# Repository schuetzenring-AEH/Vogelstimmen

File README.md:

# Vogelstimmenkasten – Waldlehrpfad (Rev 2)

Neubau der Elektronik eines Vogelstimmenkastens für den Waldlehrpfad der Kolpingfamilie.

## Überblick

Besucher können per Knopfdruck (8 beleuchtete Taster) verschiedene Vogelstimmen anhören. Die Elektronik ist auf **null Ruhestrom** optimiert (Hardware-Latch) und wird über eine 12-V-Autobatterie betrieben.

**Architektur:** DY-SV17F (IO-Trigger, integrierter Class-D-Verstärker) + Hardware-Latch (MOSFET-Selbsthaltung)

## Projektstatus

| Phase | Status |
|-------|--------|
| Anforderungen | ✅ fertig |
| Systemarchitektur (BDD/IBD) | ✅ fertig |
| Schaltplan-Dokumentation Rev 2 | ✅ fertig |
| BOM-Verfügbarkeit (LCSC/JLCPCB) | ✅ geprüft |
| Digitaler Zwilling (Bauteilebene) | ✅ `docs/digitaler_zwilling.md` |
| KiCad-Schaltplan (+ VGS-Zener D11/D12) | ✅ verdrahtet |
| PCB Rev 2.4 + Respin F-01…F-05 | ✅ Working-PCB DRC/ERC 0 Fehler |
| Gerber / BOM / CPL | ✅ `hardware/V2.5-final/` (FREIGABE MIT AUFLAGEN) |
| M04-Review / Adversarial | ✅ F-01…F-09 dispositioniert; Proto-Auflagen |
| Fertigung & Inbetriebnahme | ▶️ JLCPCB bestellbar; Proto messen vor Serie |
| MBSE-Showcase (USB) | ✅ `showcase/` + `dist/Vogelstimmen-MBSE-USB.zip` |

**Reviewer-Einstieg:** [docs/reviewer_handoff.md](docs/reviewer_handoff.md) · Checkliste [docs/review_checkliste_m04.md](docs/review_checkliste_m04.md)  
Details: **[docs/zwischenstand.md](docs/zwischenstand.md)**

## Projektstruktur

| Ordner | Inhalt |
|--------|--------|
| `docs/` | Lastenheft, Architektur, ADRs, Traceability, Zwilling, Zwischenstand |
| `hardware/V2.5-final/` | Fertigungspaket Rev 2.5 (Gerber, BOM, CPL, KiCad, PDFs) |
| `simulation/` | Interaktive Platinen-Simulation (HTML5) |
| `showcase/` | **MBSE-Präsentation** (offline Website) — `START_SHOWCASE.bat` |
| `mbse/` | Impact-Analyse, Audit, SysML/JSON-Export — URL `/mbse/` |
| `dist/` | USB-ZIP nach `tools/package_mbse_usb.ps1` |
| `rev1_archiv/` | Rev-1-Archiv (Lessons Learned) |

## Technische Eckdaten

- **Audio-Modul:** DY-SV17F (8× IO-Trigger, Mode 0, 5W Class-D, USB-Upload)
- **Versorgung:** 12V Bleiakku → TPS62163 Buck → 5V
- **Stromsparen:** Hardware-Latch — Idle ≈12 µA (R6=470 kΩ, E-RPP-01)
- **Schutz:** Verpolung SI2301+**D11 Zener 6,2 V**, Latch Q1+**D12**, TVS SMAJ15A, PTC 1A/24V
- **Zähler:** Kübler K07.90 (5V DC, elektromechanisch, Anzeige oben, zählt Aufweck-Events)
- **Taster-LEDs:** 8× beleuchtete Taster (6–24V LEDs über 12V_SW Rail)
- **Audioformat:** MP3/WAV direkt per USB auf DY-SV17F laden
- **Digitaler Zwilling:** [docs/digitaler_zwilling.md](docs/digitaler_zwilling.md)

## Rev 1 → Rev 2: Lessons Learned

Rev 1 hatte Probleme mit Spannungsfestigkeit (U4/U5 Burnout bei 12V), Bauteil-Verfügbarkeit und fehlendem Verifikationsansatz. Rev 2 verwendet:
- MBSE / V-Modell mit Traceability
- Durchgängige Spannungsprüfung aller Bauteile
- BOM-Verfügbarkeit vorab bei LCSC geprüft
- Digitaler Zwilling zur Logikverifikation

## Voraussetzungen (Entwicklung)

- [KiCad 10](https://www.kicad.org/) – Schaltplan/PCB
- Python 3 – lokale Simulation (`python simulation/serve.py`) oder `START_SHOWCASE.bat` / `START_MBSE.bat`
- [LTspice](https://www.analog.com/en/resources/design-tools-and-calculators/ltspice-simulator.html) – analoge Teilschaltungen (optional)

## Lizenz

Dieses Projekt ist für den internen Gebrauch der Kolpingfamilie bestimmt.

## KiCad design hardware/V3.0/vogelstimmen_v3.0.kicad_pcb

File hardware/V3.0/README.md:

# Fertigungspaket Rev 3.0

**Datum:** 11. August 2026  
**Projekt:** Soundplatine Waldlehrpfad · Kolping Alteglofsheim  
**KiCad:** 10.0.4 · `vogelstimmen_v3.0.kicad_*`

## Freigabe-Stand

| Check | Ergebnis |
|-------|----------|
| **DRC** | **0 Fehler**, 0 unverbunden — 1 Warnung U2 Footprint-Lib (`DRC_v3.0_final.rpt`) |
| **ERC** | siehe `ERC_v3.0_final.rpt` |
| **Widerstände** | alle **15×** `R_0603_1608Metric`, Pad-Pitch **1,65 mm** (kein 0402) |
| **Zähler** | Hengstler 0.635.128 + One-Shot (C20/R20/R21/D23/Q7/D10) |

## JLCPCB — Upload (nur SMD)

| Datei | Zweck |
|-------|--------|
| **`vogelstimmen_v3.0-Gerber.zip`** | Gerber + Drill (auch Ordner `Gerber/`) |
| **`JLCPCB_BOM.csv`** | SMT-BOM inkl. One-Shot + 0603 Basic LCSC |
| **`JLCPCB_CPL.csv`** | Pick-and-Place (52 SMT-Teile) — **diese** hochladen |
| `JLCPCB_CPL_minimal.csv` | Fallback (5 Spalten), falls volles Format scheitert |

**Nicht** an JLCPCB hochladen: `HAND_BESTUECKUNG.csv`, KiCad-Roh-CPL mit Handteilen.

**Platinen-Parameter (empfohlen):** 2 Layer · 1,6 mm · HASL oder ENIG · Clearance 0,2 mm · **Min. Bahnbreite 0,3 mm** · Via 0,6/0,3 mm.

## Handbestückung (nicht in JLCPCB-BOM)

Datei: **`HAND_BESTUECKUNG.csv`** · RS-Warenkorb: **`docs/rs_bestellliste.md`**

| Ref | Teil | Assembly | RS |
|-----|------|----------|-----|
| **U2** | DY-SV17F | HAND | nicht bei RS |
| **J5** | Hengstler **0.635.128** (nicht 0.635.132) | HAND | **312-022** |
| **J1, J2, J6** | Phoenix MPT 0,5/2 **1725656** | HAND | **220-4260** |
| **J3, J4** | Phoenix MPT 0,5/8 **1725711** | HAND | **220-4327** |
| **TP1–TP5** | Testpads | DNP | — |

## Widerstände — Package-Check (E-R0603)

| Refs | Wert | Footprint PCB | LCSC | Package |
|------|------|---------------|------|---------|
| R1,R2,R13,R20 | 100k | R_0603_1608Metric | C25803 | 0603 Basic |
| R3,R4,R9 | 10k | R_0603_1608Metric | C25804 | 0603 Basic |
| R5 | 0R | R_0603_1608Metric | C21189 | 0603 Basic |
| R6 | 470k | R_0603_1608Metric | C23178 | 0603 Basic |
| R7,R8,R11 | 4.7k | R_0603_1608Metric | C23162 | 0603 Basic |
| R10 | 1k | R_0603_1608Metric | C21190 | 0603 Basic |
| R12 | 10R | R_0603_1608Metric | C22859 | 0603 Basic |
| R21 | 100R | R_0603_1608Metric | C25796 | 0603 Basic |

Pads gemessen: **0,80×0,95 mm**, Mittenabstand **1,65 mm** → passt zu 0603 (0402 wäre ~1,0 mm).

## Änderungen gegenüber 2.5

| Thema | 2.5 | 3.0 |
|-------|-----|-----|
| Widerstände | Pads oft 0402 / LCSC 0603 → Reject | **0603 Pads + 0603 Basic LCSC** |
| Zähler J5 | Kübler K07.90 | **Hengstler 0.635.128** + One-Shot ~80 ms |
| Form | Panel / groß | Body **25,2×31 mm**, 4 Pins 15,24×25,4 mm |

## Paketinhalt

| Datei / Ordner | Inhalt |
|----------------|--------|
| `Gerber/` | Einzel-Gerber + PTH/NPTH Drill |
| `vogelstimmen_v3.0-Gerber.zip` | **Upload-Paket** |
| `JLCPCB_BOM.csv` / `JLCPCB_CPL.csv` | SMT Assembly |
| `HAND_BESTUECKUNG.csv` | Handteile |
| `RS_SCHNELLBESTELLUNG.csv` | RS-Warenkorb 1 Platine |
| `docs/rs_bestellliste.md` | RS-Links, Warnungen, 10× |
| `vogelstimmen_v3.0-schematic.pdf` | Schaltplan |
| `vogelstimmen_v3.0-pcb.pdf` | Layout |
| `docs/` | ADRs, Schaltplan, BOM-Checkliste |
| `tools/export_fab.py` | Re-Export Gerber/CPL/PDF |

## Re-Export

```powershell
& "C:\Program Files\KiCad\10.0\bin\python.exe" hardware\V3.0\tools\export_fab.py
```

## Parallel bestellen

1. JLCPCB: Gerber.zip + BOM + CPL (SMD Assembly)
2. **RS** Schnellbestellung: `RS_SCHNELLBESTELLUNG.csv` (Hengstler 312-022 + MPT) — Zähler oft Wochen
3. DY-SV17F (AliExpress; nicht bei RS)

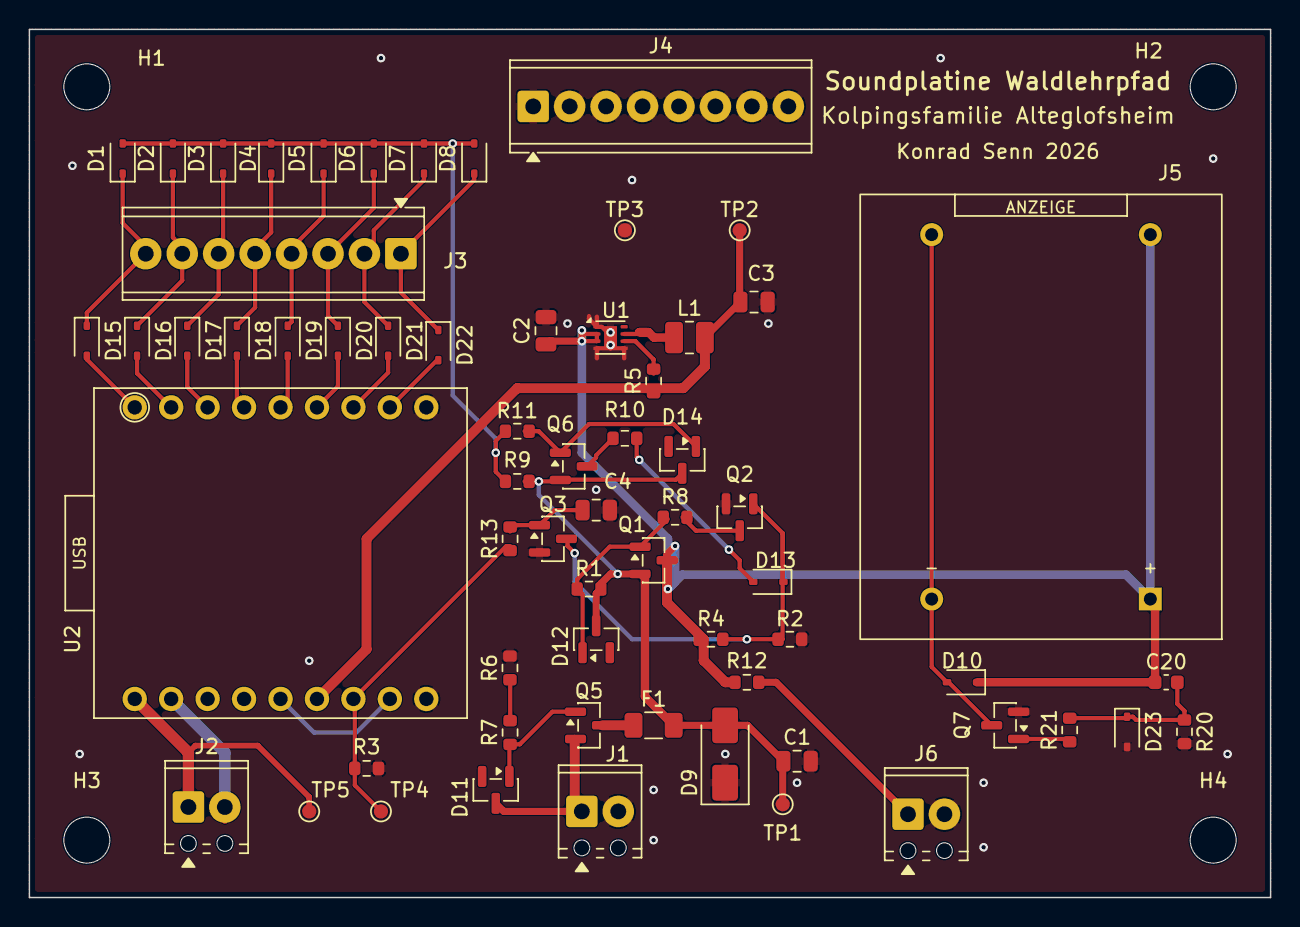
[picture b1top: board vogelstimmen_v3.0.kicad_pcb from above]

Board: 2 copper layers, 86.5 x 60.5 mm, 68 parts (0 on the bottom side), 42 nets.

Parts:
C1, C2: 10u/25V; C_0805_2012Metric
C3: 22u/10V; C_0805_2012Metric
C4: 4.7u/16V; C_0805_2012Metric
C20: 1u/25V; C_0603_1608Metric
D1, D2, D3, D4, D5, D6, D7, D8, D10, D13, D15, D16, D17, D18, D19, D20, D21, D22, D23: 1N4148WS; D_SOD-323
D9: SMAJ15A; D_SMA
D11, D12, D14: BZX84C6V2
F1: 1A/24V; Fuse_1206_3216Metric
H1, H2, H3, H4: MountingHole_3.2mm_M3
J1: MPT-0,5/2 BAT; TerminalBlock_Phoenix_MPT-0,5-2-2.54_1x02_P2.54mm_Horizontal
J2: MPT-0,5/2 SPK; TerminalBlock_Phoenix_MPT-0,5-2-2.54_1x02_P2.54mm_Horizontal
J3: MPT-0,5/8 IO; TerminalBlock_Phoenix_MPT-0,5-8-2.54_1x08_P2.54mm_Horizontal
J4: MPT-0,5/8 GND; TerminalBlock_Phoenix_MPT-0,5-8-2.54_1x08_P2.54mm_Horizontal
J5: Hengstler 0.635.128; CNT_HENGSTLER_635
J6: MPT-0,5/2 LED; TerminalBlock_Phoenix_MPT-0,5-2-2.54_1x02_P2.54mm_Horizontal
L1: 2.2uH; L_1008_2520Metric
Q1, Q5, Q6: SI2301; SOT-23
Q2, Q3: 2N7002; SOT-23
Q7: AO3400; SOT-23
R1, R2, R13, R20: 100k; R_0603_1608Metric
R3, R4, R9: 10k; R_0603_1608Metric
R5: 0R; R_0603_1608Metric
R6: 470k; R_0603_1608Metric
R7, R8, R11: 4.7k; R_0603_1608Metric
R10: 1k; R_0603_1608Metric
R12: 10; R_0603_1608Metric
R21: 100R; R_0603_1608Metric
TP1: 12V_PROT; TestPoint_Pad_D1.0mm
TP2: 5V; TestPoint_Pad_D1.0mm
TP3: GND; TestPoint_Pad_D1.0mm
TP4: BUSY; TestPoint_Pad_D1.0mm
TP5: SPK+; TestPoint_Pad_D1.0mm
U1: TPS62163; WSON-8-1EP_2x2mm_P0.5mm_EP0.9x1.6mm
U2: DY-SV17F

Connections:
/5V: C3.1, L1.2, R5.1, TP2.1 (Pin_1_1), U2.13 (V5)
/12V_LED: J6.1, R12.2
/12V_PROT: C1.1, D9.2 (A2), D12.1, D14.1, F1.2, Q1.2 (S), Q6.2, R1.2, R9.1, TP1.1 (Pin_1_1)
/12V_SW: C2.1, C20.1, D10.1 (K), J5.1, Q1.3 (D), R4.1, R12.1, U1.2 (VIN), U1.3 (EN)
/BAT+: D11.1, J1.1, Q5.2 (S)
/BTN_OR: D1.2 (A), D2.2 (A), D3.2 (A), D4.2 (A), D5.2 (A), D6.2 (A), D7.2 (A), D8.2 (A), R9.2, R11.1
/BUSY: R3.1, R13.1, TP4.1 (Pin_1_1), U2.12 (BUSY)
/CNT_GATE: Q7.1, R21.1
/CNT_LO: D10.2 (A), J5.2, Q7.3
/CNT_PULSE: C20.2, D23.1, R20.1, R21.2
/GND: C1.2, C2.2, C3.2, C4.2, D9.1 (A1), D23.2, J1.2, J4.1, J4.2, J4.3, J4.4, J4.5, J4.6, J4.7, J4.8, J6.2, Q2.2 (S), Q3.2 (S), Q7.2, R2.2, R3.2, R6.2, R20.2, TP3.1 (Pin_1_1), U1.1 (PGND), U1.4 (AGND), U1.5 (FB), U1.9 (EP), U2.9 (GND), U2.10 (CON1)
/IO0: D1.1 (K), D15.1 (K), J3.8
/IO0_M: D15.2 (A), U2.1 (IO0)
/IO1: D2.1 (K), D16.1 (K), J3.7
/IO1_M: D16.2 (A), U2.2 (IO1)
/IO2: D3.1 (K), D17.1 (K), J3.6
/IO2_M: D17.2 (A), U2.3 (IO2)
/IO3: D4.1 (K), D18.1 (K), J3.5
/IO3_M: D18.2 (A), U2.4 (IO3)
/IO4: D5.1 (K), D19.1 (K), J3.4
/IO4_M: D19.2 (A), U2.5 (IO4)
/IO5: D6.1 (K), D20.1 (K), J3.3
/IO5_M: D20.2 (A), U2.6 (IO5)
/IO6: D7.1 (K), D21.1 (K), J3.2
/IO6_M: D21.2 (A), U2.7 (IO6)
/IO7: D8.1 (K), D22.1 (K), J3.1
/IO7_M: D22.2 (A), U2.8 (IO7)
/LATCH_GATE: Q2.3 (D), R8.2
/LATCH_SET: D13.1, Q2.1 (G), Q3.3 (D), R2.1, R4.2
/Q1_GATE: D12.2, Q1.1 (G), R1.1, R8.1
/Q3_GATE: C4.1, Q3.1 (G), R13.2
/Q5_GATE: D11.2, Q5.1 (G), R7.1
/Q5_G_PD: R6.1, R7.2
/Q6_GATE: D14.2, Q6.1, R11.2
/RPP_OUT: F1.1, Q5.3 (D)
/SET_DRV: Q6.3, R10.1
/SET_PULSE: D13.2, R10.2
/SPK+: J2.1, TP5.1 (Pin_1_1), U2.18 (SPK+)
/SPK-: J2.2, U2.17 (SPK-)
/SW: L1.1, U1.7 (SW)
/V33: U2.11 (CON2), U2.14 (V33)
/VOS: R5.2, U1.6 (VOS)

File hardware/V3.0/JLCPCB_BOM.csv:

Comment,Designator,Footprint,LCSC Part #
10uF/25V 0805,"C1,C2",C_0805_2012Metric,C440198
22uF/10V 0805,C3,C_0805_2012Metric,C45783
4.7uF/16V 0805,C4,C_0805_2012Metric,C1779
1uF/25V 0603 Basic,C20,C_0603_1608Metric,C23630
1N4148WS,"D1,D2,D3,D4,D5,D6,D7,D8,D10,D13,D15,D16,D17,D18,D19,D20,D21,D22,D23",D_SOD-323,C118873
SMAJ15A,D9,D_SMA,C113958
BZX84C6V2,"D11,D12,D14",SOT-23,C179522
PTC 1A/24V 1206,F1,Fuse_1206_3216Metric,C2760272
2.2uH 1008,L1,L_1008_2520Metric,C88527
SI2301CDS,"Q1,Q5,Q6",SOT-23,C10487
2N7002LT1G,"Q2,Q3",SOT-23,C16338
AO3400,Q7,SOT-23,C20917
100k 0603 Basic,"R1,R2,R13,R20",R_0603_1608Metric,C25803
0R 0603 Basic,R5,R_0603_1608Metric,C21189
10k 0603 Basic,"R3,R4,R9",R_0603_1608Metric,C25804
10R 0603 Basic,R12,R_0603_1608Metric,C22859
100R 0603 Basic,R21,R_0603_1608Metric,C25796
470k 0603 Basic,R6,R_0603_1608Metric,C23178
4.7k 0603 Basic,"R7,R8,R11",R_0603_1608Metric,C23162
1k 0603 Basic,R10,R_0603_1608Metric,C21190
TPS62163DSGR,U1,WSON-8-1EP_2x2mm,C97534

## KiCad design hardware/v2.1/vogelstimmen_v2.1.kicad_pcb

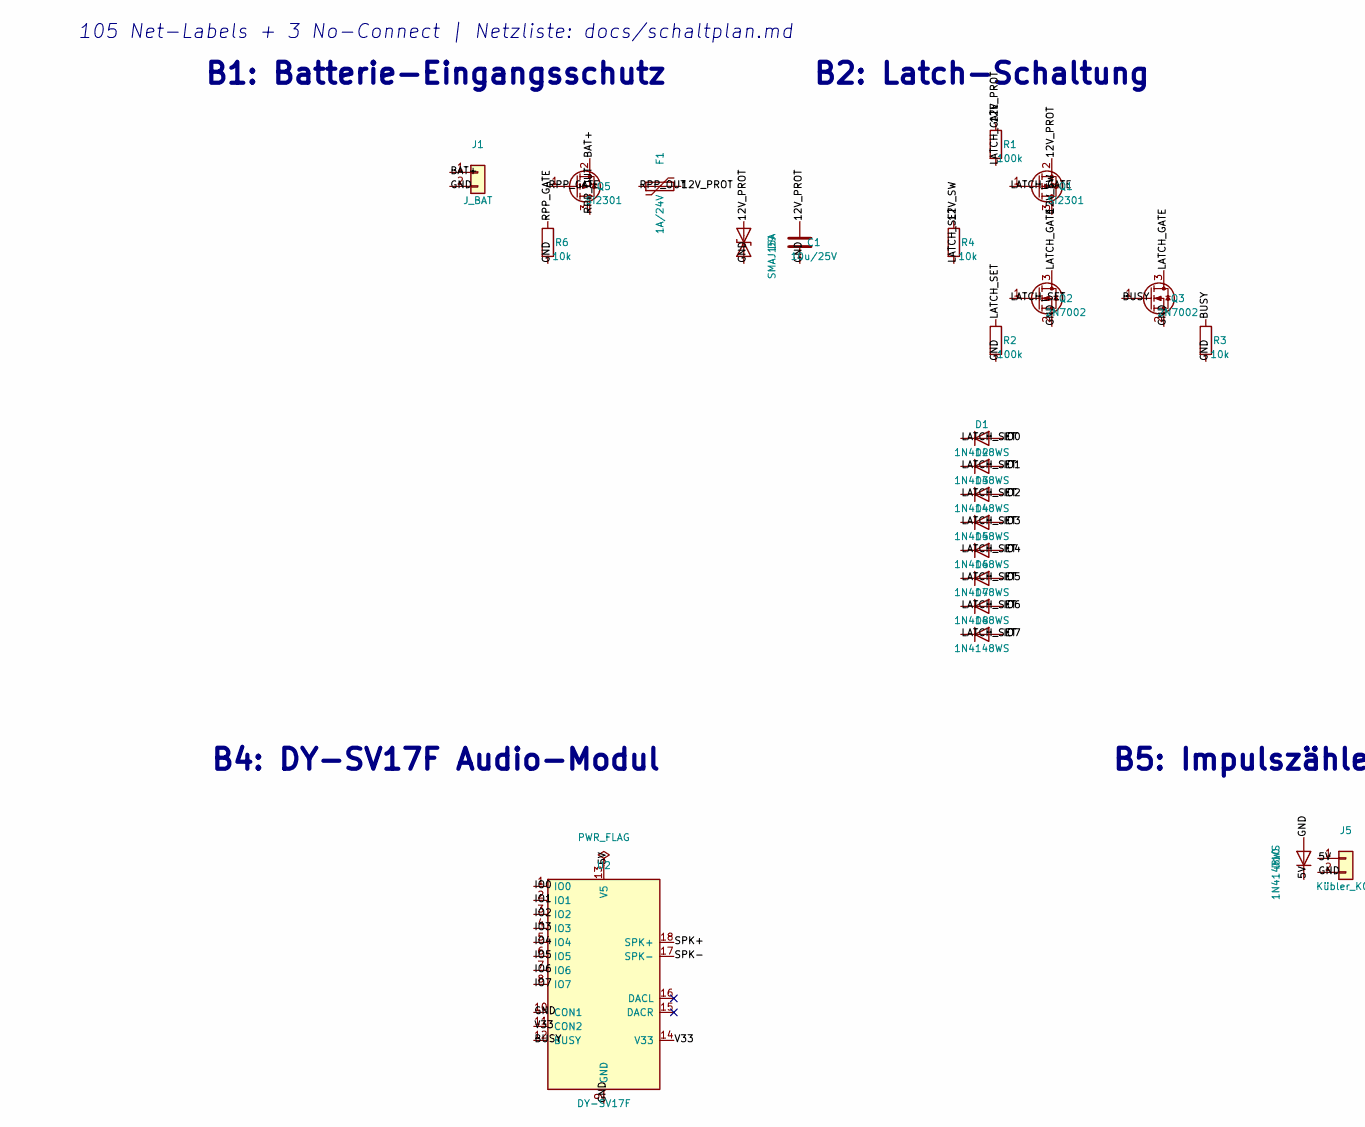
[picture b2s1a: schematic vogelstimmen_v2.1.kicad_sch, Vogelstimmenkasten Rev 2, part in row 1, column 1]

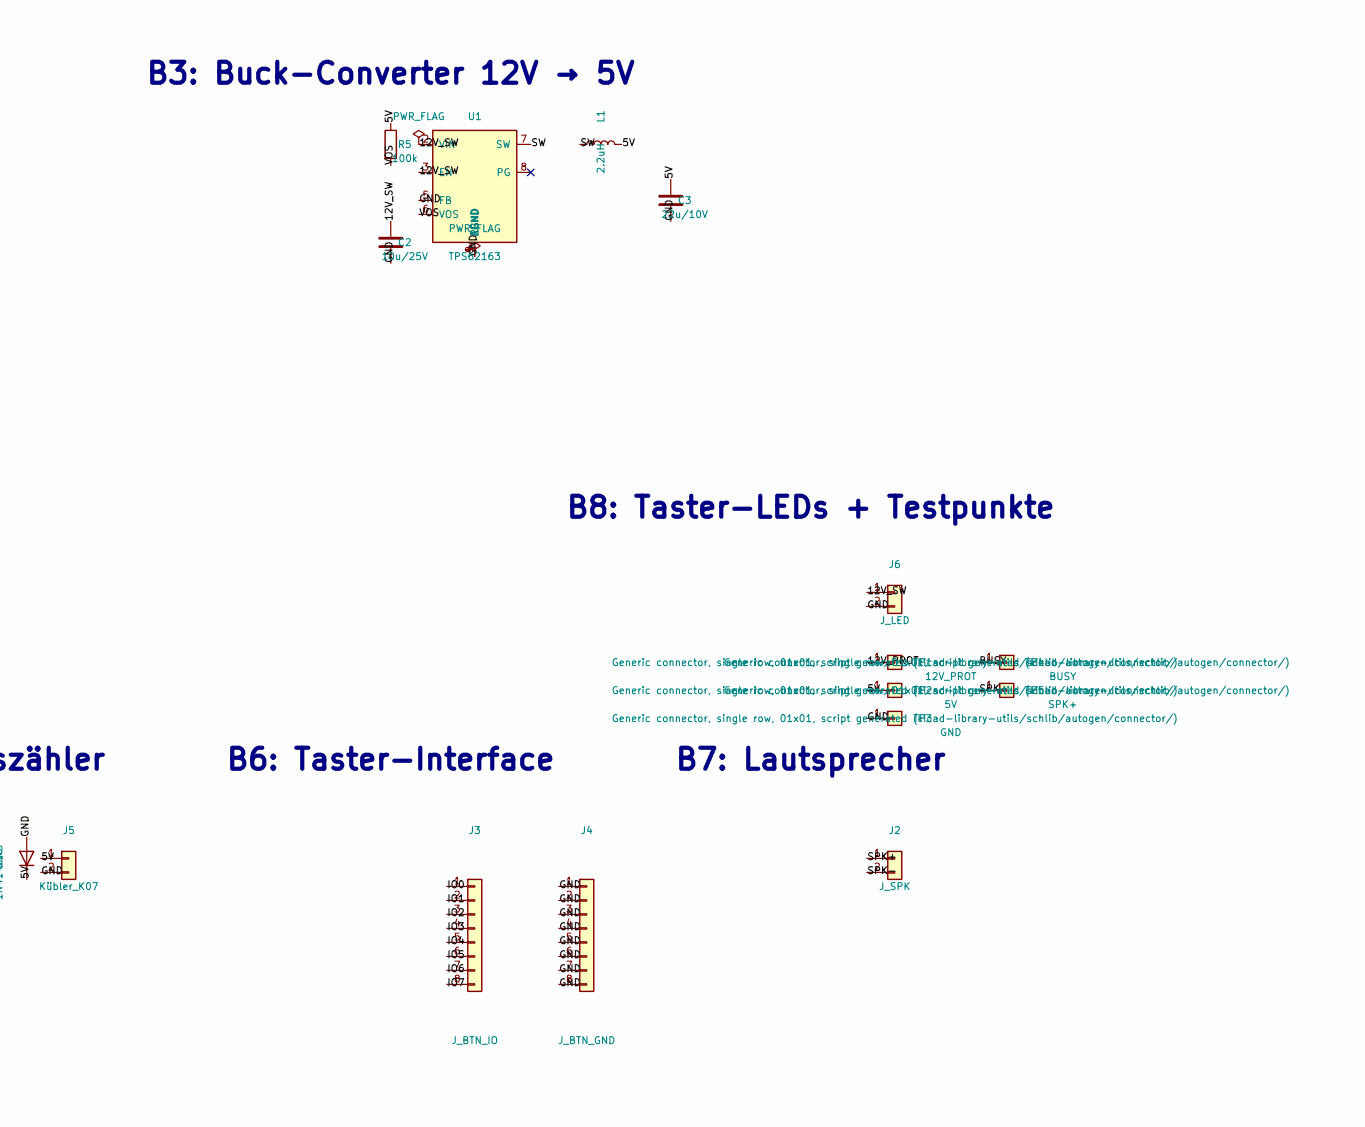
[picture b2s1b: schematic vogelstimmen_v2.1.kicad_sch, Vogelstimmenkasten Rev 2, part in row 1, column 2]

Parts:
C1, C2: 10u/25V; C_0805_2012Metric
C3: 22u/10V; C_0805_2012Metric
D1, D2, D3, D4, D5, D6, D7, D8, D10: 1N4148WS; D_SOD-323; LCSC C118873
D9: SMAJ15A; D_SMA; LCSC C113958
F1: 1A/24V; Fuse_1206_3216Metric; LCSC C2760272
J1: J_BAT; PinHeader_1x02_P2.54mm_Vertical
J2: J_SPK; PinHeader_1x02_P2.54mm_Vertical
J3: J_BTN_IO; PinHeader_1x08_P2.54mm_Vertical
J4: J_BTN_GND; PinHeader_1x08_P2.54mm_Vertical
J5: Kübler_K07; PinHeader_1x02_P2.54mm_Vertical
J6: J_LED; PinHeader_1x02_P2.54mm_Vertical
L1: 2.2uH; L_1008_2520Metric; LCSC C88527
Q1, Q5: SI2301; SOT-23; LCSC C10487
Q2, Q3: 2N7002; SOT-23; LCSC C16338
R1, R2, R5: 100k; R_0402_1005Metric
R3, R4, R6: 10k; R_0402_1005Metric
TP1: 12V_PROT; TestPoint_Pad_D1.0mm
TP2: 5V; TestPoint_Pad_D1.0mm
TP3: GND; TestPoint_Pad_D1.0mm
TP4: BUSY; TestPoint_Pad_D1.0mm
TP5: SPK+; TestPoint_Pad_D1.0mm
U1: TPS62163; WSON-8-1EP_2x2mm_P0.5mm_EP0.9x1.6mm; LCSC C97534
U2: DY-SV17F

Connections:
/5V: C3.1, D10.1 (K), J5.1, L1.2, R5.1, TP2.1 (Pin_1_1), U2.13 (V5)
/12V_PROT: C1.1, D9.2 (A2), F1.2, Q1.2 (S), R1.1, TP1.1 (Pin_1_1)
/12V_SW: C2.1, J6.1, Q1.3 (D), R4.1, U1.2 (VIN), U1.3 (EN)
/BAT+: J1.1, Q5.2 (S)
/BUSY: Q3.1 (G), R3.1, TP4.1 (Pin_1_1), U2.12 (BUSY)
/GND: C1.2, C2.2, C3.2, D9.1 (A1), D10.2 (A), J1.2, J4.1, J4.2, J4.3, J4.4, J4.5, J4.6, J4.7, J4.8, J5.2, J6.2, Q2.2 (S), Q3.2 (S), R2.2, R3.2, R6.2, TP3.1 (Pin_1_1), U1.1 (PGND), U1.4 (AGND), U1.5 (FB), U1.9 (EP), U2.9 (GND), U2.10 (CON1)
/IO0: D1.2 (A), J3.1, U2.1 (IO0)
/IO1: D2.2 (A), J3.2, U2.2 (IO1)
/IO2: D3.2 (A), J3.3, U2.3 (IO2)
/IO3: D4.2 (A), J3.4, U2.4 (IO3)
/IO4: D5.2 (A), J3.5, U2.5 (IO4)
/IO5: D6.2 (A), J3.6, U2.6 (IO5)
/IO6: D7.2 (A), J3.7, U2.7 (IO6)
/IO7: D8.2 (A), J3.8, U2.8 (IO7)
/LATCH_GATE: Q1.1 (G), Q2.3 (D), Q3.3 (D), R1.2
/LATCH_SET: D1.1 (K), D2.1 (K), D3.1 (K), D4.1 (K), D5.1 (K), D6.1 (K), D7.1 (K), D8.1 (K), Q2.1 (G), R2.1, R4.2
/RPP_GATE: Q5.1 (G), R6.1
/RPP_OUT: F1.1, Q5.3 (D)
/SPK+: J2.1, TP5.1 (Pin_1_1), U2.18 (SPK+)
/SPK-: J2.2, U2.17 (SPK-)
/SW: L1.1, U1.7 (SW)
/V33: U2.11 (CON2), U2.14 (V33)
/VOS: R5.2, U1.6 (VOS)

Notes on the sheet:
B1: Batterie-Eingangsschutz
B2: Latch-Schaltung
B3: Buck-Converter 12V → 5V
B4: DY-SV17F Audio-Modul
B5: Impulszähler
B6: Taster-Interface
B7: Lautsprecher
B8: Taster-LEDs + Testpunkte
105 Net-Labels + 3 No-Connect | Netzliste: docs/schaltplan.md

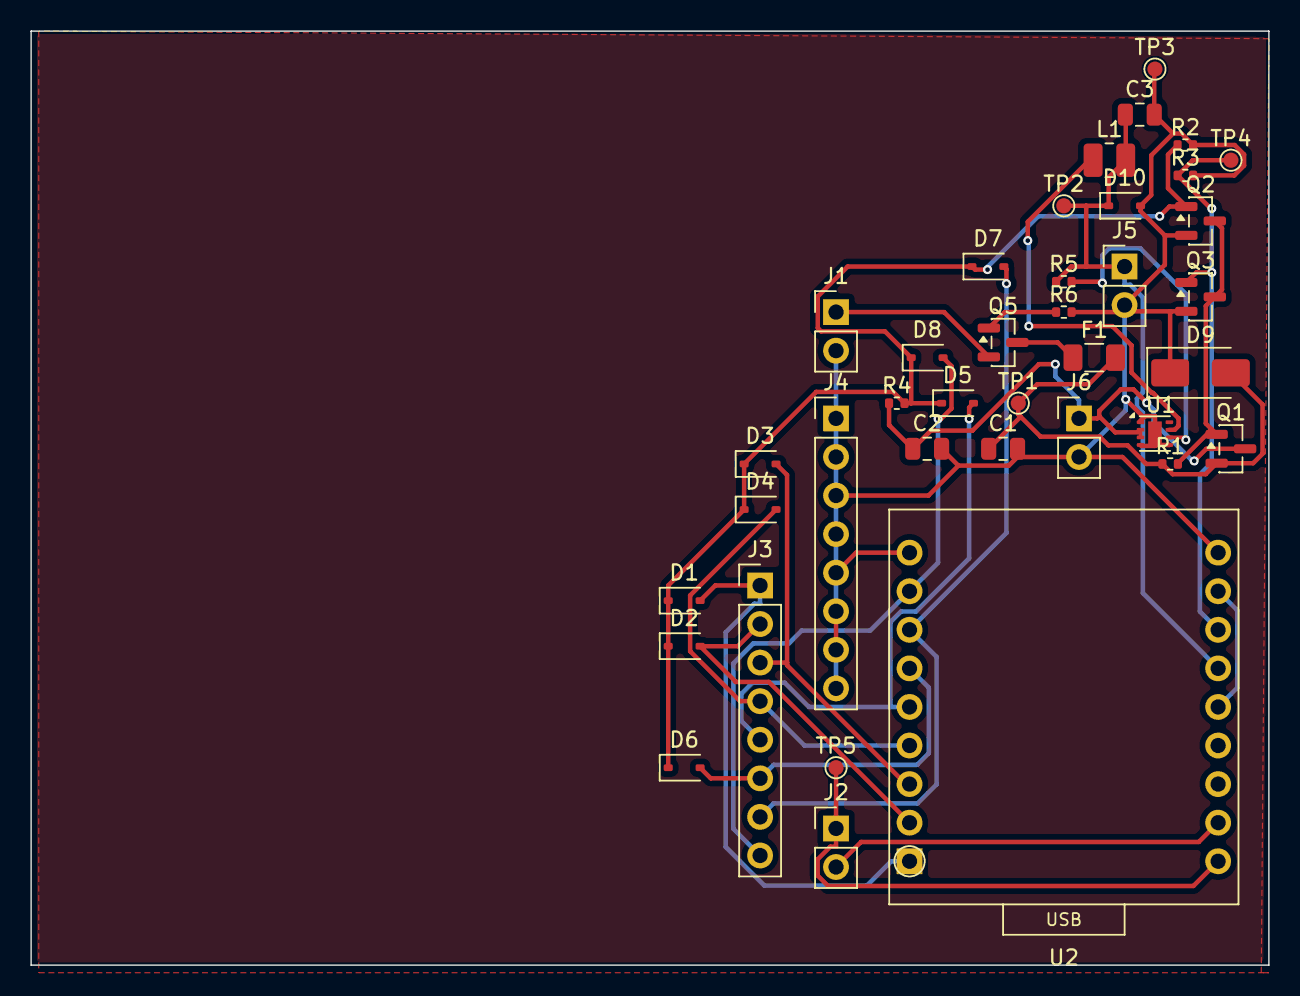
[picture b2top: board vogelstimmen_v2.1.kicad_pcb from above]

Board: 2 copper layers, 81.5 x 61.5 mm, 38 parts (0 on the bottom side), 23 nets.

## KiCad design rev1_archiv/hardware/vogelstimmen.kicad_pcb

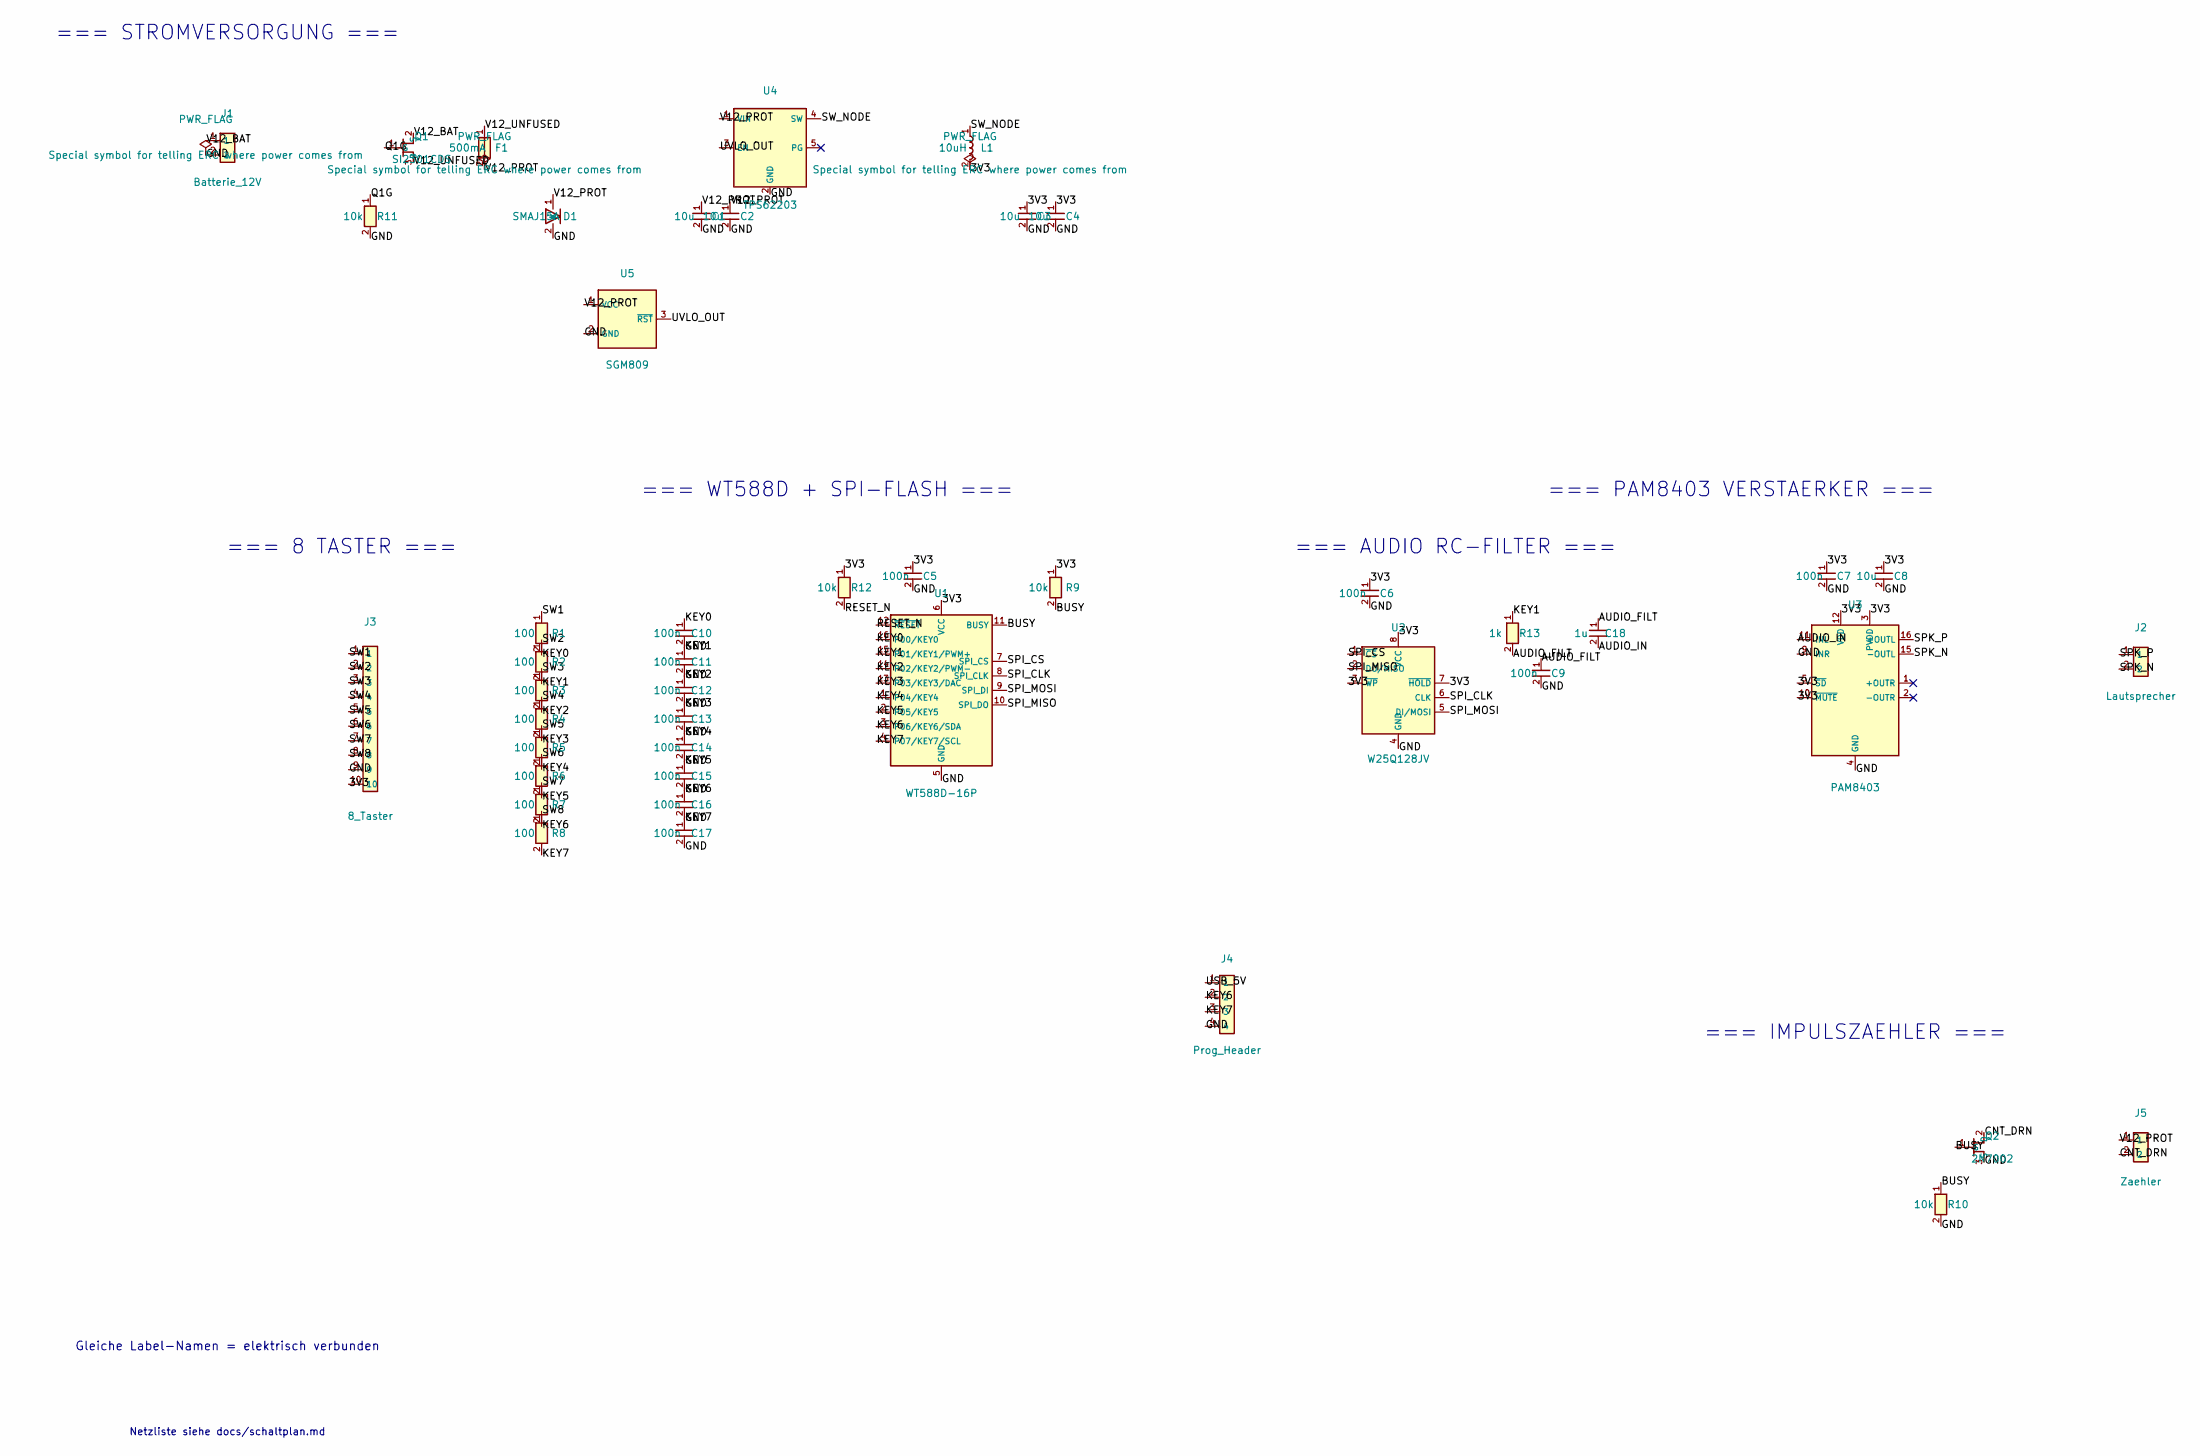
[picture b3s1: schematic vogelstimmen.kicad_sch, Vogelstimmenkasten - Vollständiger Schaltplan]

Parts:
C1, C2, C3, C4, C8: 10u; C_0805_2012Metric
C5, C6, C7, C9, C10, C11, C12, C13, C14, C15, C16, C17: 100n; C_0805_2012Metric
C18: 1u; C_0805_2012Metric
D1: SMAJ15A; D_SMA
F1: 500mA; Fuse_1206_3216Metric
J1: Batterie_12V; PinHeader_1x02_P2.54mm_Vertical
J2: Lautsprecher; PinHeader_1x02_P2.54mm_Vertical
J3: 8_Taster; PinHeader_1x10_P2.54mm_Vertical
J4: Prog_Header; PinHeader_1x04_P2.54mm_Vertical
J5: Zaehler; PinHeader_1x02_P2.54mm_Vertical
L1: 10uH; L_1210_3225Metric
Q1: SI2301CDS; SOT-23
Q2: 2N7002; SOT-23
R1, R2, R3, R4, R5, R6, R7, R8: 100; R_0805_2012Metric
R9, R10, R11, R12: 10k; R_0805_2012Metric
R13: 1k; R_0805_2012Metric
U1: WT588D-16P; DIP-16_W7.62mm
U2: W25Q128JV; SOIC-8_3.9x4.9mm_P1.27mm
U3: PAM8403; SOP-16_4.4x10.4mm_P1.27mm
U4: TPS62203; SOT-23-5
U5: SGM809; SOT-23

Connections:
/3V3: C3.1, C4.1, C5.1, C6.1, C7.1, C8.1, J3.10, L1.2, R9.1, R12.1, U1.6 (VCC), U2.3 (~WP), U2.7 (~HOLD), U2.8 (VCC), U3.3 (PVDD), U3.5 (~SD), U3.10 (~MUTE), U3.12 (VDD)
/AUDIO_FILT: C9.1, C18.1, R13.2
/AUDIO_IN: C18.2, U3.11 (INL)
/BUSY: Q2.1 (G), R9.2, R10.1, U1.11 (BUSY)
/CNT_DRN: J5.2, Q2.2 (D)
/GND: C1.2, C2.2, C3.2, C4.2, C5.2, C6.2, C7.2, C8.2, C9.2, C10.2, C11.2, C12.2, C13.2, C14.2, C15.2, C16.2, C17.2, D1.2 (A), J1.2, J3.9, J4.4, Q2.3 (S), R10.2, R11.2, U1.5 (GND), U2.4 (GND), U3.4 (GND), U3.9 (INR), U4.2 (GND), U5.2 (GND)
/KEY0: C10.1, R1.2, U1.16 (P00/KEY0)
/KEY1: C11.1, R2.2, R13.1, U1.15 (P01/KEY1/PWM+)
/KEY2: C12.1, R3.2, U1.14 (P02/KEY2/PWM-)
/KEY3: C13.1, R4.2, U1.13 (P03/KEY3/DAC)
/KEY4: C14.1, R5.2, U1.1 (P04/KEY4)
/KEY5: C15.1, R6.2, U1.2 (P05/KEY5)
/KEY6: C16.1, J4.2, R7.2, U1.3 (P06/KEY6/SDA)
/KEY7: C17.1, J4.3, R8.2, U1.4 (P07/KEY7/SCL)
/Q1G: Q1.1 (G), R11.1
/RESET_N: R12.2, U1.12 (~RESET)
/SPI_CLK: U1.8 (SPI_CLK), U2.6 (CLK)
/SPI_CS: U1.7 (SPI_CS), U2.1 (~CS)
/SPI_MISO: U1.10 (SPI_DO), U2.2 (DO/MISO)
/SPI_MOSI: U1.9 (SPI_DI), U2.5 (DI/MOSI)
/SPK_N: J2.2, U3.15 (-OUTL)
/SPK_P: J2.1, U3.16 (+OUTL)
/SW1: J3.1, R1.1
/SW2: J3.2, R2.1
/SW3: J3.3, R3.1
/SW4: J3.4, R4.1
/SW5: J3.5, R5.1
/SW6: J3.6, R6.1
/SW7: J3.7, R7.1
/SW8: J3.8, R8.1
/SW_NODE: L1.1, U4.4 (SW)
/USB_5V: J4.1
/UVLO_OUT: U4.3 (EN), U5.3 (~RST)
/V12_BAT: J1.1, Q1.2 (S)
/V12_PROT: C1.1, C2.1, D1.1 (K), F1.2, J5.1, U4.1 (VIN), U5.1 (VCC)
/V12_UNFUSED: F1.1, Q1.3 (D)

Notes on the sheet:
=== IMPULSZAEHLER ===
=== AUDIO RC-FILTER ===
=== STROMVERSORGUNG ===
Netzliste siehe docs/schaltplan.md
=== WT588D + SPI-FLASH ===
=== 8 TASTER ===
=== PAM8403 VERSTAERKER ===
Gleiche Label-Namen = elektrisch verbunden

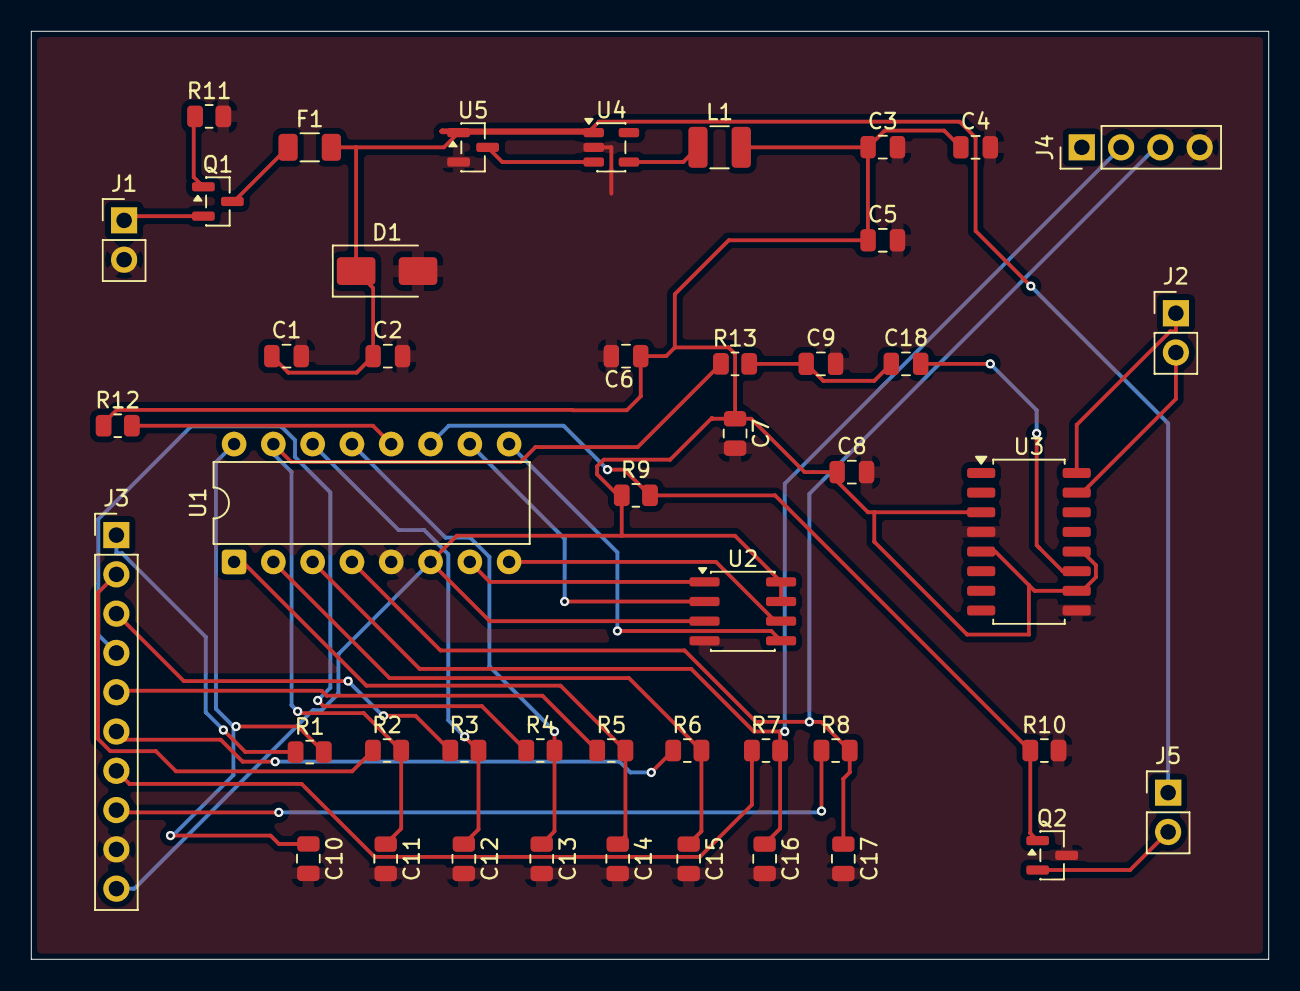
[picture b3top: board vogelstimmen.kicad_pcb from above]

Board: 2 copper layers, 80.0 x 60.0 mm, 46 parts (0 on the bottom side), 35 nets.

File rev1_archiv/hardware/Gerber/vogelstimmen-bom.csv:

Comment,Designator,Footprint,LCSC Part #
10uF,"C1,C2,C3,C4,C8",C0805,C440198
100nF,"C5,C6,C7,C9,C10,C11,C12,C13,C14,C15,C16,C17",C0805,C49678
1uF,C18,C0805,C28323
SMAJ15A,D1,SMA,C23424
500mA,F1,F1206,C7202014
10uH,L1,L1210,C76835
SI2301CDS,Q1,SOT-23,C10487
2N7002,Q2,SOT-23,C8545
100,"R1,R2,R3,R4,R5,R6,R7,R8",R0805,C17408
10k,"R9,R10,R11,R12",R0805,C17414
1k,R13,R0805,C17513
W25Q128JV,U2,SOIC-8,C97521
PAM8403DR-H,U3,SOP-16,C17337
TPS62203DBVR,U4,SOT-23-5,C9051
SGM809,U5,SOT-23,C699615
